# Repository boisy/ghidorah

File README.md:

# Ghidorah

Ghidorah is a protocol for passing information between computers linked together using a specially constructed RS-232 cable. Ghidorah employs a ring topology; each computer on the ring uses Cooperative Message Passing (CMP) to ensure that the message finds its way to its intended destination. The message's routing path is complete when the arbiter receives the message back from its round trip.

The TRS-80 Color Computer family is currently supported, but in theory, any computer with an RS-232 port can be part of the ring.

## Definitions

* Arbiter: a computer on the ring that is responsible for originating messages. There can only be one arbiter. An arbiter's nodex is always 0.
* Listener: a computer on the ring that listens for messages. A listener's nodex can be between 1 and 254.
* Message: a stream of data that has both a header and a data payload.
* Nodex: a number between 0 and 254 that uniquely identifies a node on the ring.
* Ring: the physical cable that connects the arbiter and listeners together.

## Commands

There are Python 3 commands for several common operations.

For convenience, you can set the `GHIDORAH_DEVICE` environment variable on the arbiter to the serial device. 

### Discover

This is the first message that should be sent to all listeners on the ring. This forces each listener to assign itself an ID, and tells the arbiter how many listeners are on the ring.

Note: If any other message is sent prior to this one, the listeners ignore it!

Example:

`python3 discover.py --device /dev/cu.usbserial-FTVCW8GB0 --baud 57600`

Replace the device with the appropriate name for your arbiter. You can leave off the `--baud 57600` since it's the default.

### Identity

This command identifies the type of machine that is listening.

Note: If any other message is sent prior to this one, the listeners ignore it!

Example 1: Identify all listeners on the ring.

`python3 identify.py --device /dev/cu.usbserial-FTVCW8GB0`

Example 2: Identify a particular listener on the ring.

`python3 identify.py --device /dev/cu.usbserial-FTVCW8GB0 --nodex 2`

### Setup

This command can be used in place of `discover.py` since it does a Discovery, performs an Identity, and if there are only CoCo 3s on the ring, puts them in high-speed mode. In that case, subsequent commands should use `--baud 115200`.

Example: Setup all listeners on the ring.

`python3 setup.py --device /dev/cu.usbserial-FTVCW8GB0`

### Read
This command reads memory from a listener and returns the bytes.

Example: Read 256 bytes from location $6000 from listener 1:

`python3 read.py --device /dev/cu.usbserial-FTVCW8GB0 --readaddr 0x6000 --readlen 0x100 --nodex 1`

### Load
This command writes bytes to a listener's memory. Optionally, it can execute at an address.               

Example 1: Load the contents of the file `test.raw` into the memory of listener 3 at address $0700:

`python3 load.py --device /dev/cu.usbserial-FTVCW8GB0 --file test.raw --loadaddr 0x700 --nodex 3`

Example 2: Load the contents of the file `game.raw` into the memory of listener 3 at address $0700 and execute at that address:

`python3 load.py --device /dev/cu.usbserial-FTVCW8GB0 --file game.raw --loadaddr 0x700 --execaddr 0x700 --nodex 3`

### LoadM
This command behaves similar to the Load command, except that it can properly load Disk BASIC compatible .BIN files. Also, the code will automatically execute once loaded.

Example: Load the contents of the file `LANCER.BIN` into the memory of listener 2 and start the game:

`python3 loadm.py --device /dev/cu.usbserial-FTVCW8GB0 --file LANCER.BIN --nodex 2`

## Messages

Ghidorah uses messages to pass information between listeners. Here are the supported messages:

### Discovery Message

The Discovery Message is sent by the arbiter to discover who is on the ring. It must be the first message a listener receives. If a listener receives any other message before the Discovery Message, it will ignore that message and simply relay it to the next listener.

* Byte 0: <0x44>
* Byte 1: <Source Nodex>
* Byte 2: 0
* Bytes 3 to 21: Don't Care

Each listener that receives the message shall:

  1. Increment the value in Byte 2.
  2. Obtain the incremented value in Byte 2 and save it as its nodex.
  3. Send the message to the next listener.

Once the arbiter receives the message, it may investigate Byte 2 which holds the number of listeners on the ring.

### Identity Message

The Identity Message is sent by the arbiter to determine specific information about a listener.

* Byte 0: <0x49>
* Byte 1: <Source Nodex>
* Byte 2: <Destination Nodex> (0 to 254, or 255 for everyone)
* Bytes 3 to 21: Don't Care

Each listener shall examine Byte 2 and compare it to its nodex. If there is no match, the listener shall:

  1. Send the message to the next listener.

If the nodex matches, the listener shall:

  1. Set Byte 3 to the major revision of the client software.
  2. Set Byte 4 to the minor revision of the client software.
  3. Set Byte 5 to the maximum supported baud rate (0 = 57600, 1 = 115200).
  4. Set Bytes 6 to 15 to a 10 character string identifying the machine type.
  5. Send the message to the next listener.

### Read Message

The Read Message is sent by the arbiter to obtain data from memory for a given listener.

* Byte 0: <0x52>
* Byte 1: <Source Nodex>
* Byte 2: <Destination Nodex> (0 to 254, or 255 for everyone)
* Byte 3: Bits 15 to 8 of read address
* Byte 4: Bits 7 to 0 of read address
* Byte 5: Read limit (1 to 16)
* Bytes 6 to 21: Don't Care

Each listener shall examine Byte 2 and compare it to its nodex. If there is no match, the listener shall:

  1. Send the message to the next listener.

If the nodex matches, the listener shall:

  1. Obtain the 16 bit address in Bytes 3 and 4 and the limit in Byte 5.
  2. Copy 'limit' bytes from its memory at the specified address to Bytes 6 to (5+'limit') in the message.
  3. Send the message to the next listener.

### Write Message

The Write Message is sent by the arbiter to write data to memory for a given listener.

* Byte 0: <0x57>
* Byte 1: <Source Nodex>
* Byte 2: <Destination Nodex> (0 to 254, or 255 for everyone)
* Byte 3: Bits 15 to 8 of write address
* Byte 4: Bits 7 to 0 of write address
* Byte 5: Write limit (1 to 16)
* Bytes 6 to 21: Data to write

Each listener shall examine Byte 2 and compare it to its nodex. If there is no match, the listener shall:

  1. Send the message to the next listener.

If the nodex matches, the listener shall:

  1. Obtain the 16 bit address in Bytes 3 and 4 and the limit in Byte 5.
  2. Copy 'limit' bytes from Bytes 6 to (5+'limit') of the message to its memory at the specified address.
  3. Send the message to the next listener.

### Execute Message

The Execute Message is sent by the arbiter to direct the listener to start executing at an address in its memory.

* Byte 0: <0x45>
* Byte 1: <Source Nodex>
* Byte 2: <Destination Nodex> (0 to 254, or 255 for everyone)
* Byte 3: Bits 15 to 8 of execution address
* Byte 4: Bits 7 to 0 of execution address
* Bytes 5 to 21: Don't care

Each listener shall examine Byte 2 and compare it to its nodex. If there is no match, the listener shall:

  1. Send the message to the next listener.

If the nodex matches, the listener shall:

  1. Obtain the 16 bit address in Bytes 3 and 4.
  2. Send the message to the next listener.
  3. Direct its CPU to start executing at the specified address.

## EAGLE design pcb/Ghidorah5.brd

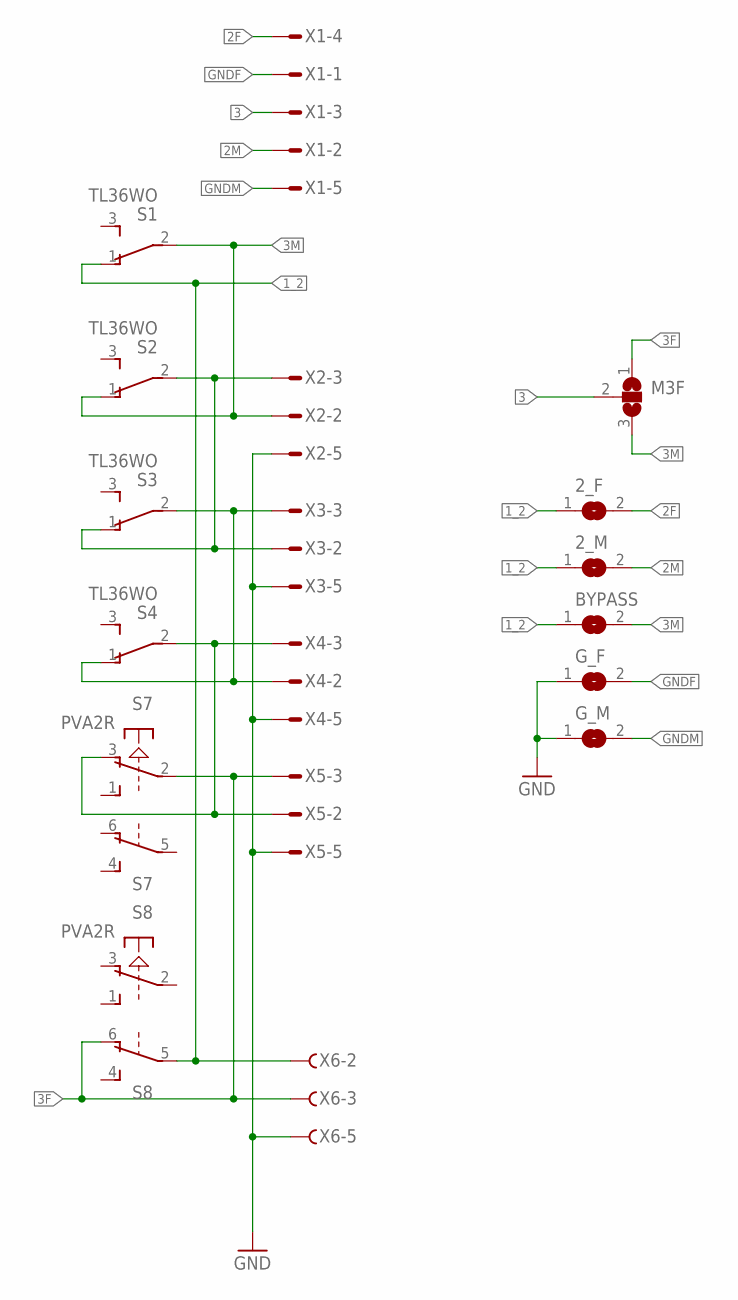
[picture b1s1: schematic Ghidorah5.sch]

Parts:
2_F, 2_M: SJ
BYPASS: SJ
G_F: SJ
G_M: SJ
M3F: SJ2W; SJ_2
S1, S2, S3, S4: TL36WO; TL3XWO
S7, S8: PVA2R
X1, X2, X3, X4: M09DS; M09D
X5: M09VS; M09V
X6: F09VS; F09V

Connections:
1_2: 2_F.1, 2_M.1, BYPASS.1, S1.1 (O), S8.5, X6.2
2F: 2_F.2, X1.4
2M: 2_M.2, X1.2
3: M3F.2, X1.3
3F: M3F.1, S7.2, S8.6 (O), X5.3, X6.3
3M: BYPASS.2, M3F.3, S1.2, S2.1 (O), X2.2
GND: G_F.1, G_M.1, X2.5, X3.5, X4.5, X5.5, X6.5
GNDF: G_F.2, X1.1
GNDM: G_M.2, X1.5
unnamed: S2.2, S3.1 (O), X2.3, X3.2
unnamed: S3.2, S4.1 (O), X3.3, X4.2
unnamed: S4.2, S7.3 (O), X4.3, X5.2

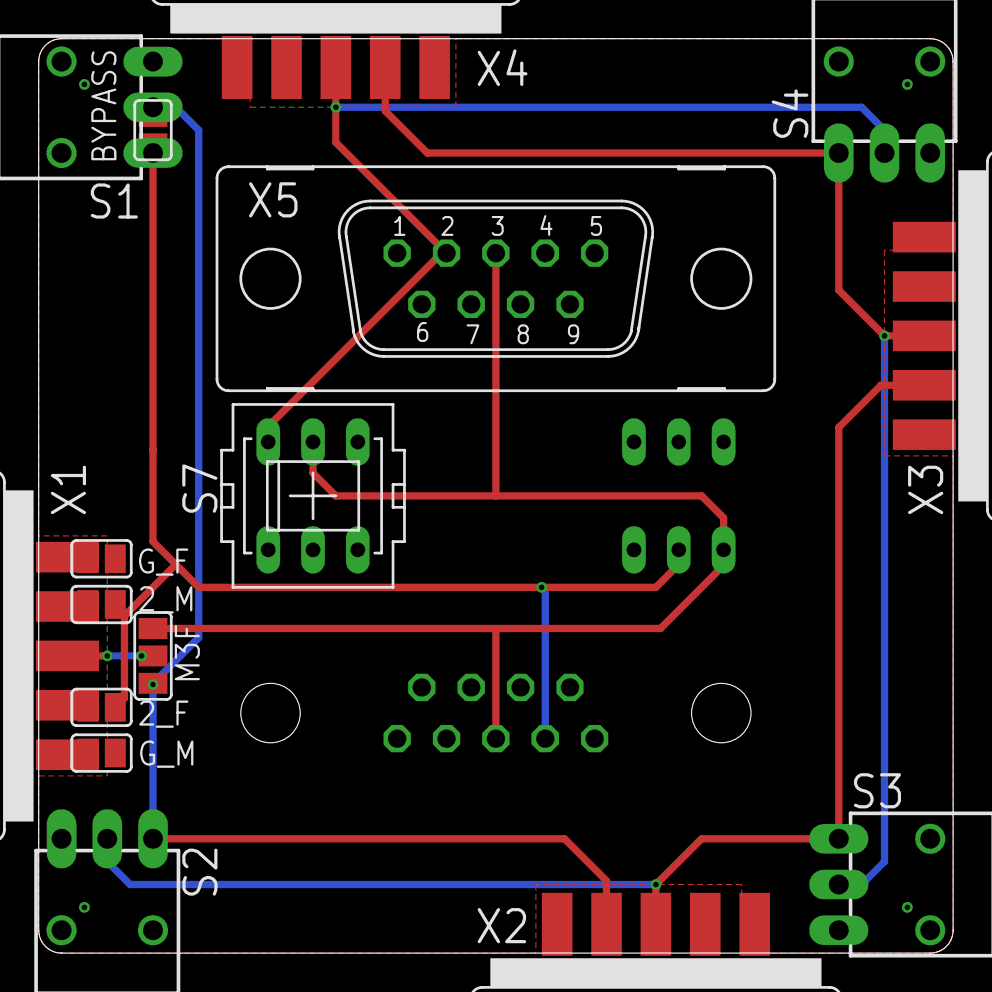
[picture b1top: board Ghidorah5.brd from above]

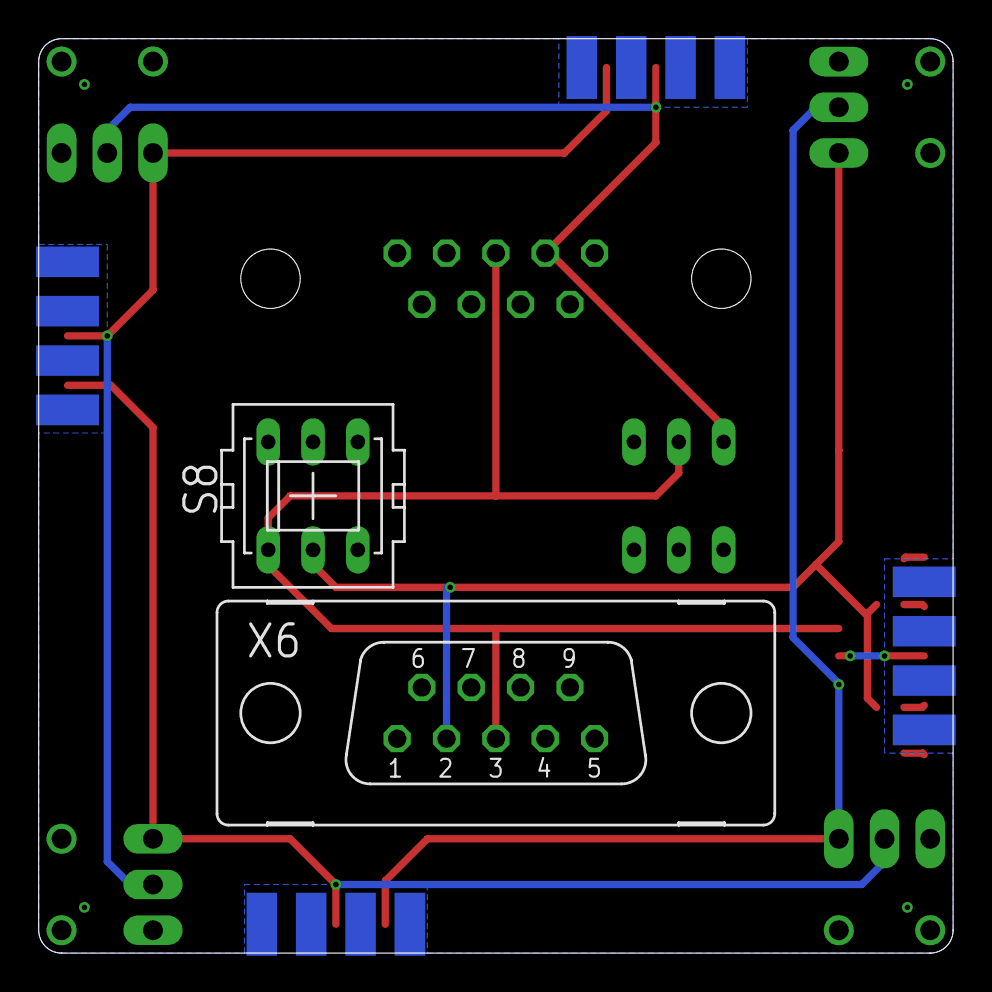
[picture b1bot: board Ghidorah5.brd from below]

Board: 2 copper layers, 50.8 x 50.8 mm, 18 parts (2 on the bottom side), 12 nets.

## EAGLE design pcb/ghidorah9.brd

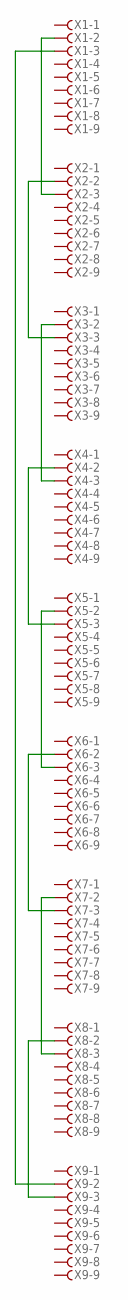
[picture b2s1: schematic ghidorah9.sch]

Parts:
X1, X2, X3, X4, X5, X6, X7, X8: F09DS; F09D
X9: F09VS; F09V

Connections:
unnamed: X1.2, X2.3
unnamed: X2.2, X3.3
unnamed: X3.2, X4.3
unnamed: X4.2, X5.3
unnamed: X5.2, X6.3
unnamed: X6.2, X7.3
unnamed: X7.2, X8.3
unnamed: X8.2, X9.3
unnamed: X1.3, X9.2

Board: 2 copper layers, 9 parts (0 on the bottom side), 9 nets, no tracks yet.

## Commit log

2020-11-01 Adding sources
2020-11-02 Fixed parentheses issue
2020-11-28 Fixed misspelling
2020-12-02 Added LOADM functionality in ghidorah.py and a stand-alone LOADM command
2020-12-02 Cleaned up some assumptions in the code, made _exec into execute(), fixed a few commands
2020-12-03 Fixed issue with identity() in ghidorah.py, now returns a proper string that can be compared. Fixed setup.py to kick all CoCo 3s into high speed mode *IF* there are ONLY CoCo 3s on the ring.
2020-12-03 Updating README
2020-12-03 Read command now returns the byte array, and updated README
2020-12-03 Added support for fast loads in loadm.py
2020-12-03 Correcting assumptions in fast loadm
2020-12-03 Optimized fast/slow POKE code
2020-12-03 Minor assumption about CoCo speed fixed
2020-12-03 Removed unnecessary length parameter in write()
2020-12-03 Fixed assumption about lo/hi speed mode in loadm fast load
2020-12-04 Added error return value on Ghidorah functions to detect timeout condition
2021-01-02 Added GHIDORAH_DEVICE environment variable.
2021-01-02 Fixed misspelling.
2021-01-02 Making improvements to the internals of ghidorah.py
2021-01-02 Fixed read in ghidorah.py to return bytestream
2021-01-03 Fixed read() function in ghidorah.py to return correct data
2021-01-03 Fixed mistakes in help
2021-01-03 More fixes
2021-01-04 Cleaning up Makefile, removing .raw and replacing with .bin
2021-01-28 Fixed error in autoexec.bas and failure in makefile
2021-03-09 Added a --raw option to output to straight binary
2021-05-23 Add PCB artwork
2021-05-23 Revert autoexec.bas change

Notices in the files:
parts and their libraries:
SparkFun: Licensing: CC v3.0 Share-Alike You are welcome to use this library for commercial purposes.
